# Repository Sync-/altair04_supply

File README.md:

# altair04_supply
A ultra wide input voltage range supply based on the Altair04-900 application circuit

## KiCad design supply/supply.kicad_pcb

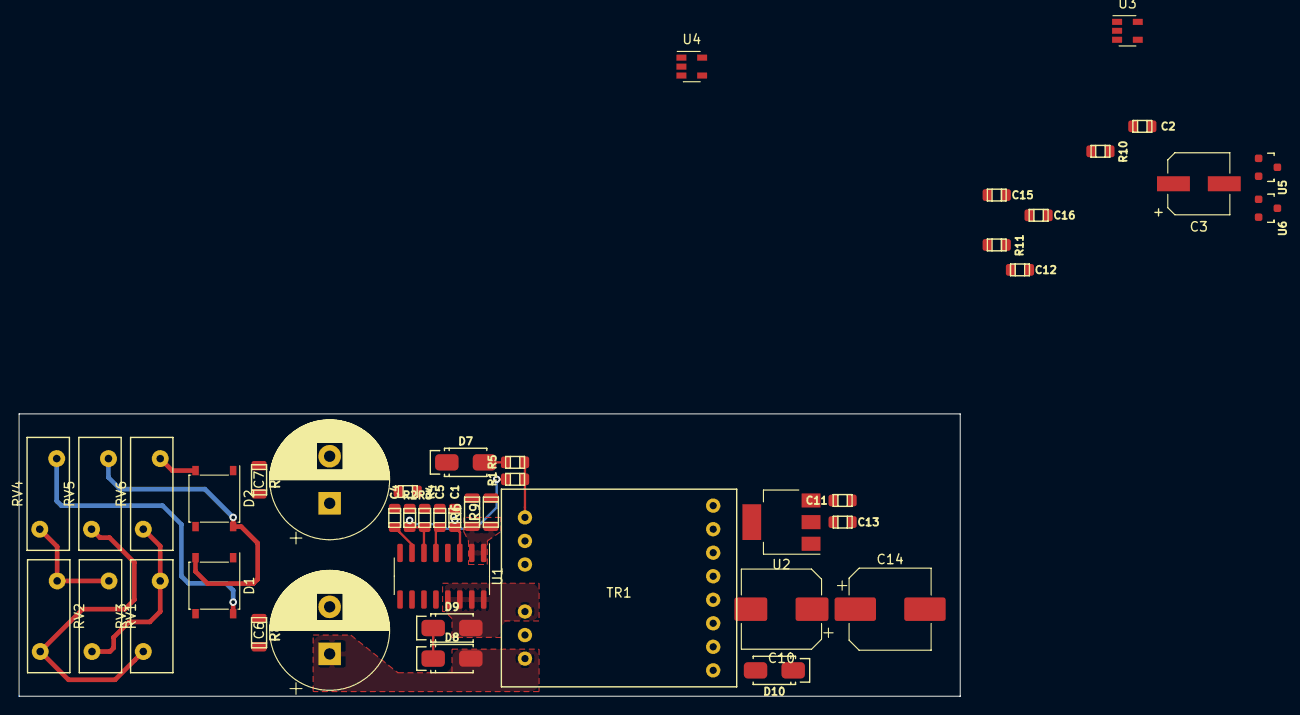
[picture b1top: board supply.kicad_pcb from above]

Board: 2 copper layers, 100.0 x 30.0 mm, 44 parts (0 on the bottom side), 30 nets.

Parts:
C1, C11, C13, C16: 100n; C_0805
C2: 1n; C_0805
C3: 2.2µ; CP_Elec_6.3x4.5
C4: 470n; C_0805
C5: 4.7n; C_0805
C6, C7: 47µ; CP_Radial_D12.5mm_P5.00mm
C10: 470µ; CP_Elec_8x10
C12, C15: 1µ; C_0805
C14: 470µ; CP_Elec_8x10.5
D1, D2: D_Bridge_+A-A; Diode_Bridge_MBLS
D7, D9, D10: D; SMA_Standard
D8: 1.5KExxA; SMA_Standard
R1: 33k; R_0805
R2, R4: 8.2k; R_0805
R3: 51k; R_0805
R5: 0; R_0805
R6: 1.3; R_1206
R7, R8: 6.8M; R_1206
R9: DNP; R_1206
R10: 330; R_0805
R11: 2.7k; R_0805
RV1, RV2, RV3, RV4, RV5, RV6: Varistor; RV_Disc_D12mm_W4.5mm_P7.5mm
TR1: 750871110
U1: ALTAIR04-900; SOIC-16_3.9x9.9mm_P1.27mm
U2: AP1117-50; SOT-223-3_TabPin2
U3: MCP73811T-420I-OT; SOT-23-5
U4: AP9101CK; SOT-23-5
U5, U6: NFET; SOT-23

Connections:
+5V: C12.1, C13.1, C14.1, U2.2, U3.1, U3.4, U3.5
/COMP: C2.1, C4.1, U1.7
/DRN: D9.2, TR1.4, U1.13, U1.14, U1.15, U1.16
/FB: R1.2, R2.1, R3.1, U1.6
/IREF: C5.1, U1.5
/SRC: R6.1, R9.1, U1.1, U1.2
/VCC: C1.1, C3.1, D7.1, U1.3
DC+: C6.1, D1.1, D2.1, D8.2, R7.1, TR1.6
GND: C1.2, C2.2, C3.2, C5.2, C7.2, D1.3, D2.3, R2.2, R3.2, R4.2, R6.2, R8.2, R9.2, TR1.3, U1.4
GNDA: C10.2, C11.1, C12.2, C13.2, C14.2, C15.2, R11.2, TR1.12, TR1.14, U2.1, U3.2, U5.2
L1: RV1.2, RV2.2, RV4.2
L2: RV2.1, RV3.2, RV5.2
L3: RV1.1, RV3.1, RV6.2
unnamed: C15.1, R10.2, U3.3
unnamed: C16.2, U4.3, U6.2
unnamed: C4.2, R4.1
unnamed: C6.2, C7.1, R7.2, R8.1
unnamed: C10.1, C11.2, D10.1, U2.3
unnamed: C16.1, R10.1, U4.2
unnamed: D1.2, D2.4, RV5.1
unnamed: D1.4, RV4.1
unnamed: D2.2, RV6.1
unnamed: D7.2, R5.2
unnamed: D8.1, D9.1
unnamed: D10.2, TR1.7, TR1.9
unnamed: R1.1, R5.1, TR1.1
unnamed: R11.1, U4.1
unnamed: U4.4, U6.1
unnamed: U4.5, U5.1
unnamed: U5.3, U6.3

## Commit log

2019-05-02 Primary side schematic
2019-05-02 Add Li charger/protection
2019-05-06 stuff
2019-05-06 add altair04 symbol
2019-05-10 add xfmr footprint
